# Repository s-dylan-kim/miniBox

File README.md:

# WakBox

A RP2040 powered hitbox style controller PCB, housing, and firmware built by me.

### Required Materials
- PCB
- Case/Housing
- 6 Heat set sockets
- 6 screws (type TBA)
- 5 6x6x5 mm tactile switches
- 12 kailh choc 2 switches
- 11 24mm pushbutton keycaps
- 1 30mm pushbutton keycap 

## PCB

## Schematic

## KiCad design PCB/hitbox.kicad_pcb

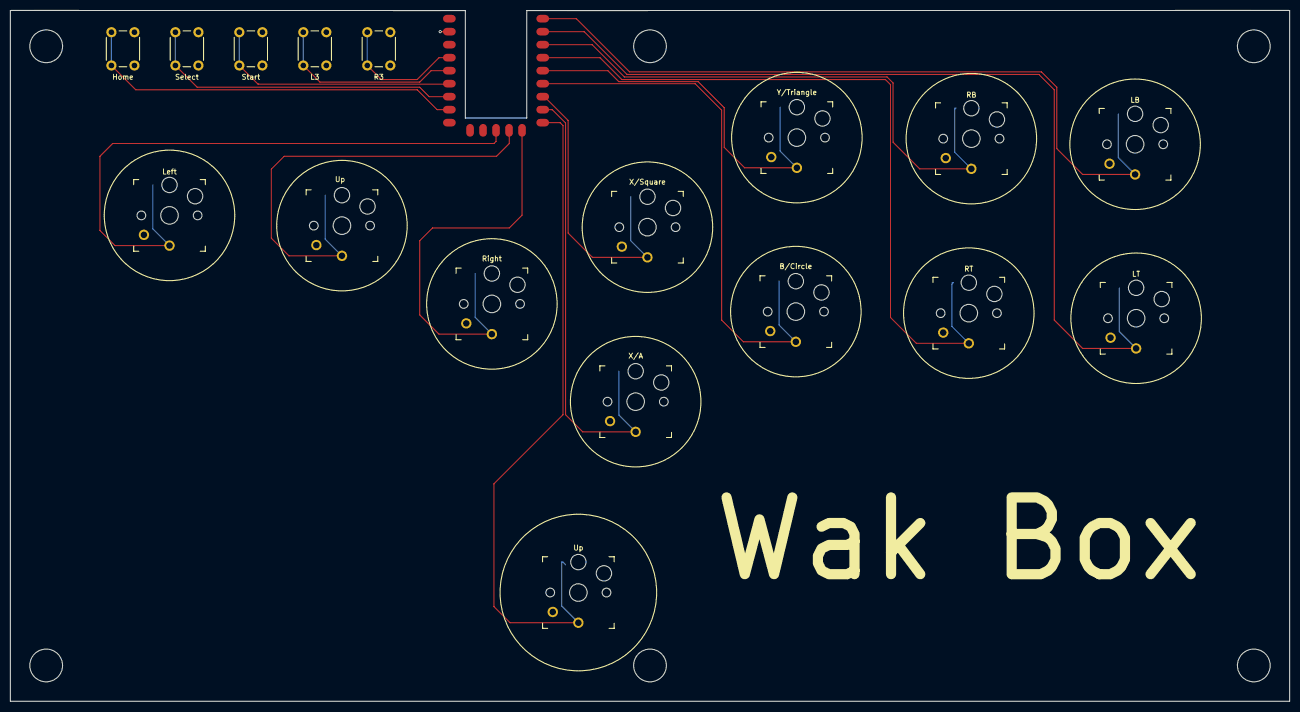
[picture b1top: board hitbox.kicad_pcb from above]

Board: 2 copper layers, 250.0 x 135.0 mm, 18 parts (0 on the bottom side), 18 nets.

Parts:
B/Circle: SW_Push; Kailh_socket_PG1350_optional
Home: SW_Push; SW_PUSH_6mm_H5mm
L3: SW_Push; SW_PUSH_6mm_H5mm
LB: SW_Push; Kailh_socket_PG1350_optional
LT: SW_Push; Kailh_socket_PG1350_optional
Left: SW_Push; Kailh_socket_PG1350_optional
R3: SW_Push; SW_PUSH_6mm_H5mm
RB: SW_Push; Kailh_socket_PG1350_optional
RT: SW_Push; Kailh_socket_PG1350_optional
Right: SW_Push; Kailh_socket_PG1350_optional
Select: SW_Push; SW_PUSH_6mm_H5mm
Start: SW_Push; SW_PUSH_6mm_H5mm
U1: rp2040-zero; rp2040-zero-smd
Up: SW_Push; Kailh_socket_PG1350_optional
Up#2: SW_Push; Kailh_socket_PG1350_optional
X/A: SW_Push; Kailh_socket_PG1350_optional
X/Square: SW_Push; Kailh_socket_PG1350_optional
Y/Triangle: SW_Push; Kailh_socket_PG1350_optional

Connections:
A/X: U1.8 (7), X/A.1
B/Circle: B/Circle.1, U1.6 (5)
Down: U1.11 (10), Up.1
GND: B/Circle.2, Home.2, L3.2, LB.2, LT.2, Left.2, R3.2, RB.2, RT.2, Right.2, Select.2, Start.2, U1.22 (GND), Up.2, Up#2.2, X/A.2, X/Square.2, Y/Triangle.2
Home: Home.1, U1.16 (15)
L3: L3.1, U1.19 (28)
Left: Left.1, U1.12 (11)
Left Bumper: LB.1, U1.1 (0)
Left Trigger: LT.1, U1.2 (1)
R3: R3.1, U1.20 (29)
Right: Right.1, U1.10 (9)
Right Bumper: RB.1, U1.3 (2)
Right Trigger: RT.1, U1.4 (3)
Select: Select.1, U1.17 (26)
Start: Start.1, U1.18 (27)
Up: U1.9 (8), Up#2.1
X/Square: U1.7 (6), X/Square.1
Y/Triangle: U1.5 (4), Y/Triangle.1

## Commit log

2024-03-26 Add KiCad project
2024-03-26 add gitignore
2024-03-26 add to readme
2024-03-26 fix schematic image in readme
